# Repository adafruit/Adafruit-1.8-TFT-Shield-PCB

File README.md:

## Adafruit 1.8" 18-bit Color TFT Shield w/microSD and Joystick PCB

<a href="http://www.adafruit.com/products/802"><br/>
Click here to purchase one from the Adafruit shop</a>

PCB files for the Adafruit 1.8" 18-bit Color TFT Shield. Format is EagleCAD schematic and board layout
* https://www.adafruit.com/product/802

### Description

This lovely little shield is the best way to add a small, colorful and bright display to any project. We took our popular 1.8" TFT breakout board and remixed it into an Arduino shield complete with microSD card slot and a 5-way joystick navigation switch and three selection buttons! Since the display uses only 4 pins to communicate and has its own pixel-addressable frame buffer, it can be used easily to add a display & interface without exhausting the memory or pins.

New! We've updated this shield to be 'Arduino R3' format compatible so you can now use it with any and all Arduinos or Metros - including the Metro M0 or M4, Arduino Mega, Zero, etc. We also use Adafruit seesaw for the TFT backlight, TFT reset, and button inputs - you can query the buttons and joystick over I2C now, so only 2 pins are needed to communicate with all 8 switches.

The 1.8" display has 128x160 color pixels. Unlike the low cost "Nokia 6110" and similar LCD displays, which are CSTN type and thus have poor color and slow refresh, this display is a true TFT! The TFT driver (ST7735R) can display full 18-bit color (262,144 shades!).

The shield has the TFT display soldered on (it uses a delicate flex-circuit connector) as well as a ultra-low-dropout 3.3V regulator and a 3/5V level shifter so its safe to use with 3V or 5V Arduino compatibles. We also had some space left over so we placed a microSD card holder (so you can easily load full color bitmaps from a FAT16/FAT32 formatted microSD card), a 5-way navigation switch (left, right, up, down, select) and three tactile buttons marked A BC. The microSD card is not included, but you can pick one up here.

If you just want to display text, shapes, lines, pixels, etc the shield uses the SPI pins (SCK/MOSI/MISO), I2C pins (SDA & SCL) and digital #8. For the microSD card, you'll also give up Digital #4. This shield works with any Arduino UNO and compatibles, Mega, Zero, etc. If it's shield compatible, you're good to go.

### License

Adafruit invests time and resources providing this open source design, please support Adafruit and open-source hardware by purchasing products from [Adafruit](https://www.adafruit.com)!

Designed by Limor Fried/Ladyada for Adafruit Industries.

Creative Commons Attribution/Share-Alike, all text above must be included in any redistribution. See license.txt for additional details.

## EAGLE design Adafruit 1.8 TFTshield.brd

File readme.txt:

Adafruit 1.8" 18-bit Color TFT Shield w/microSD and Joystick 

These are the Eagle CAD files for the Adafruit 1.8" 18-bit Color TFT Shield w/microSD and Joystick - for Arduino:
  ----> http://www.adafruit.com/products/802

Adafruit invests time and resources providing this open source design, please support Adafruit and open-source hardware by purchasing products from Adafruit!

This lovely little shield is the best way to add a small, colorful and bright display to any project. We took our popular 1.8" TFT breakout board and remixed it into an Arduino shield complete with microSD card slot and a 5-way joystick navigation switch (with a nice plastic knob)! Since the display uses only 4 pins to communicate and has its own pixel-addressable frame buffer, it can be used easily to add a display & interface without exhausting the memory or pins. 

All text above must be included in any redistribution

Designed by Limor Fried/Ladyada for Adafruit Industries.
Creative Commons Attribution/Share-Alike, all text above must be included in any redistribution

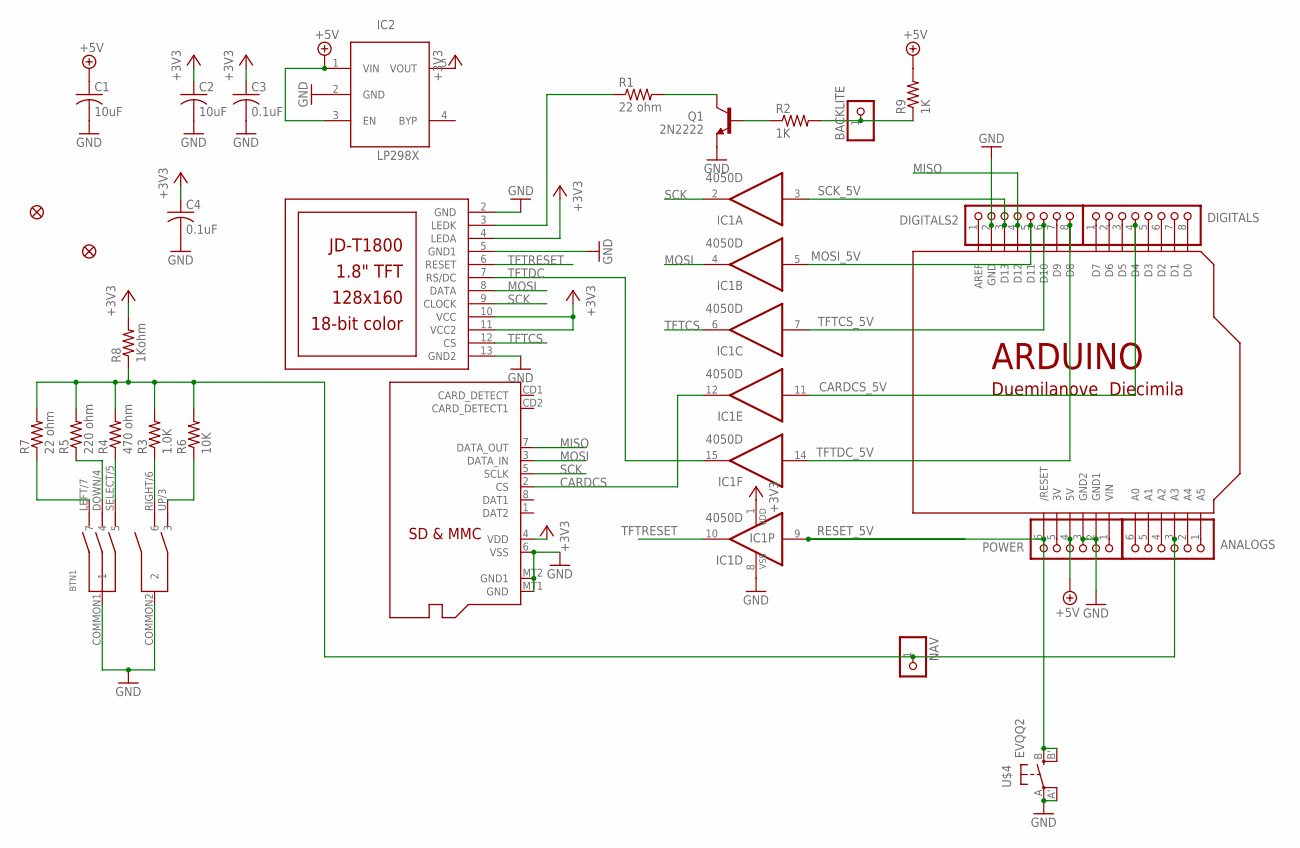
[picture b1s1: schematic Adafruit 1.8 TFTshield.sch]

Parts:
ANALOGS: PINHD-1X6CB; 1X06-CLEANBIG
BACKLITE: PINHD-1X1; 1X01
BTN1: SWITCH_4WAY_TPA511GLFS
C1, C2: 10uF; C0805K
C3, C4: 0.1uF; C0805K
DIGITALS, DIGITALS2: PINHD-1X8CLEANBIG; 1X08-CLEANBIG
FID1, FID3: FIDUCIAL1X2.5; FIDUCIAL-1X2.5
IC1: 4050D; SO16
IC2: RT9193-33GB; SOT23-5L
NAV: PINHD-1X1; 1X01
POWER: PINHD-1X6CB; 1X06-CLEANBIG
Q1: 2N2222; SOT23-BEC
R1, R7: 22 ohm; R0805
R2, R9: 1K; R0805
R3: 1.0K; R0805
R4: 470 ohm; R0805
R5: 220 ohm; R0805
R6: 10K; R0805
R8: 1Kohm; R0805
U$1: JD-T1800
U$2: ARDUINOUNO; ARDUINO
U$3: MICROSD
U$4: EVQQ2; EVQ-Q2

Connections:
+3V3: C2.1, C3.1, C4.1, IC1.1 (VDD), IC2.5 (VOUT), R8.2, U$1.4 (LEDA), U$1.10 (VCC), U$1.11 (VCC2), U$3.4 (VDD)
+5V: C1.1, IC2.1 (VIN), IC2.3 (EN), POWER.4, R9.2, U$2.5V
CARDCS: IC1.12 (O), U$3.2 (CS)
CARDCS_5V: DIGITALS.4, IC1.11 (I), U$2.D4
GND: BTN1.COMMON1 (1), BTN1.COMMON2 (2), C1.2, C2.2, C3.2, C4.2, DIGITALS2.2, IC1.8 (VSS), IC2.2 (GND), POWER.2, POWER.3, Q1.E, U$1.2 (GND), U$1.5 (GND1), U$1.13 (GND2), U$2.GND, U$2.GND1, U$2.GND2, U$3.6 (VSS), U$3.MT1 (GND), U$3.MT2 (GND1), U$4.A, U$4.A' (P1)
MISO: DIGITALS2.4, U$2.D12, U$3.7 (DATA_OUT)
MOSI: IC1.4 (O), U$1.8 (DATA), U$3.3 (DATA_IN)
MOSI_5V: DIGITALS2.5, IC1.5 (I), U$2.D11
unnamed: Q1.B, R2.1
unnamed: BTN1.LEFT/7 (7), R7.1
unnamed: BTN1.DOWN/4 (4), R5.1
unnamed: R1.1, U$1.3 (LEDK)
unnamed: Q1.C, R1.2
unnamed: DIGITALS2.7, U$2.D9
unnamed: BTN1.SELECT/5 (5), R4.1
unnamed: BTN1.RIGHT/6 (6), R3.1
unnamed: BTN1.UP/3 (3), R6.1
unnamed: ANALOGS.3, NAV.1, R3.2, R4.2, R5.2, R6.2, R7.2, R8.1, U$2.A3
unnamed: DIGITALS.1, U$2.D7
unnamed: DIGITALS.2, U$2.D6
unnamed: DIGITALS.3, U$2.D5
unnamed: DIGITALS.5, U$2.D3
unnamed: DIGITALS.6, U$2.D2
unnamed: DIGITALS.7, U$2.D1
unnamed: DIGITALS.8, U$2.D0
unnamed: DIGITALS2.1, U$2.AREF
unnamed: ANALOGS.1, U$2.A5
unnamed: ANALOGS.2, U$2.A4
unnamed: ANALOGS.4, U$2.A2
unnamed: ANALOGS.5, U$2.A1
unnamed: ANALOGS.6, U$2.A0
unnamed: POWER.1, U$2.VIN
unnamed: POWER.5, U$2.3V
unnamed: BACKLITE.1, R2.2, R9.1
RESET_5V: IC1.9 (I), POWER.6, U$2.RESET (/RESET), U$4.B (S), U$4.B' (S1)
SCK: IC1.2 (O), U$1.9 (CLOCK), U$3.5 (SCLK)
SCK_5V: DIGITALS2.3, IC1.3 (I), U$2.D13
TFTCS: IC1.6 (O), U$1.12 (CS)
TFTCS_5V: DIGITALS2.6, IC1.7 (I), U$2.D10
TFTDC: IC1.15 (O), U$1.7 (RS/DC)
TFTDC_5V: DIGITALS2.8, IC1.14 (I), U$2.D8
TFTRESET: IC1.10 (O), U$1.6 (RESET)

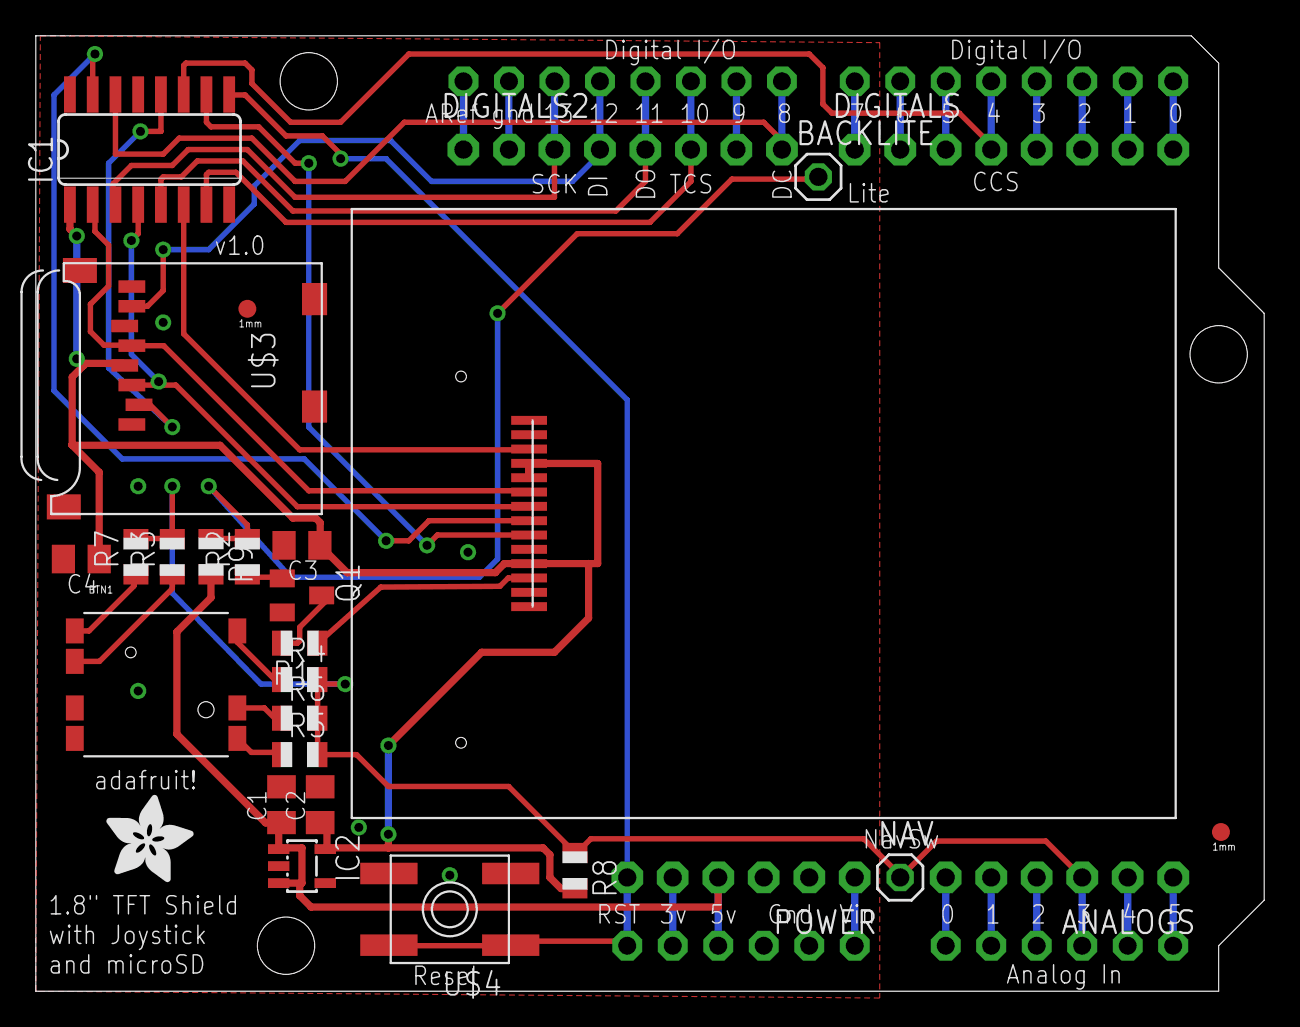
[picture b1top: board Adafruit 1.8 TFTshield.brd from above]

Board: 2 copper layers, 68.6 x 53.3 mm, 31 parts (1 on the bottom side), 42 nets.

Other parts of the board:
U$5: ADAFRUIT_TEXT_30MM
U$6: ADAFRUIT_5MM

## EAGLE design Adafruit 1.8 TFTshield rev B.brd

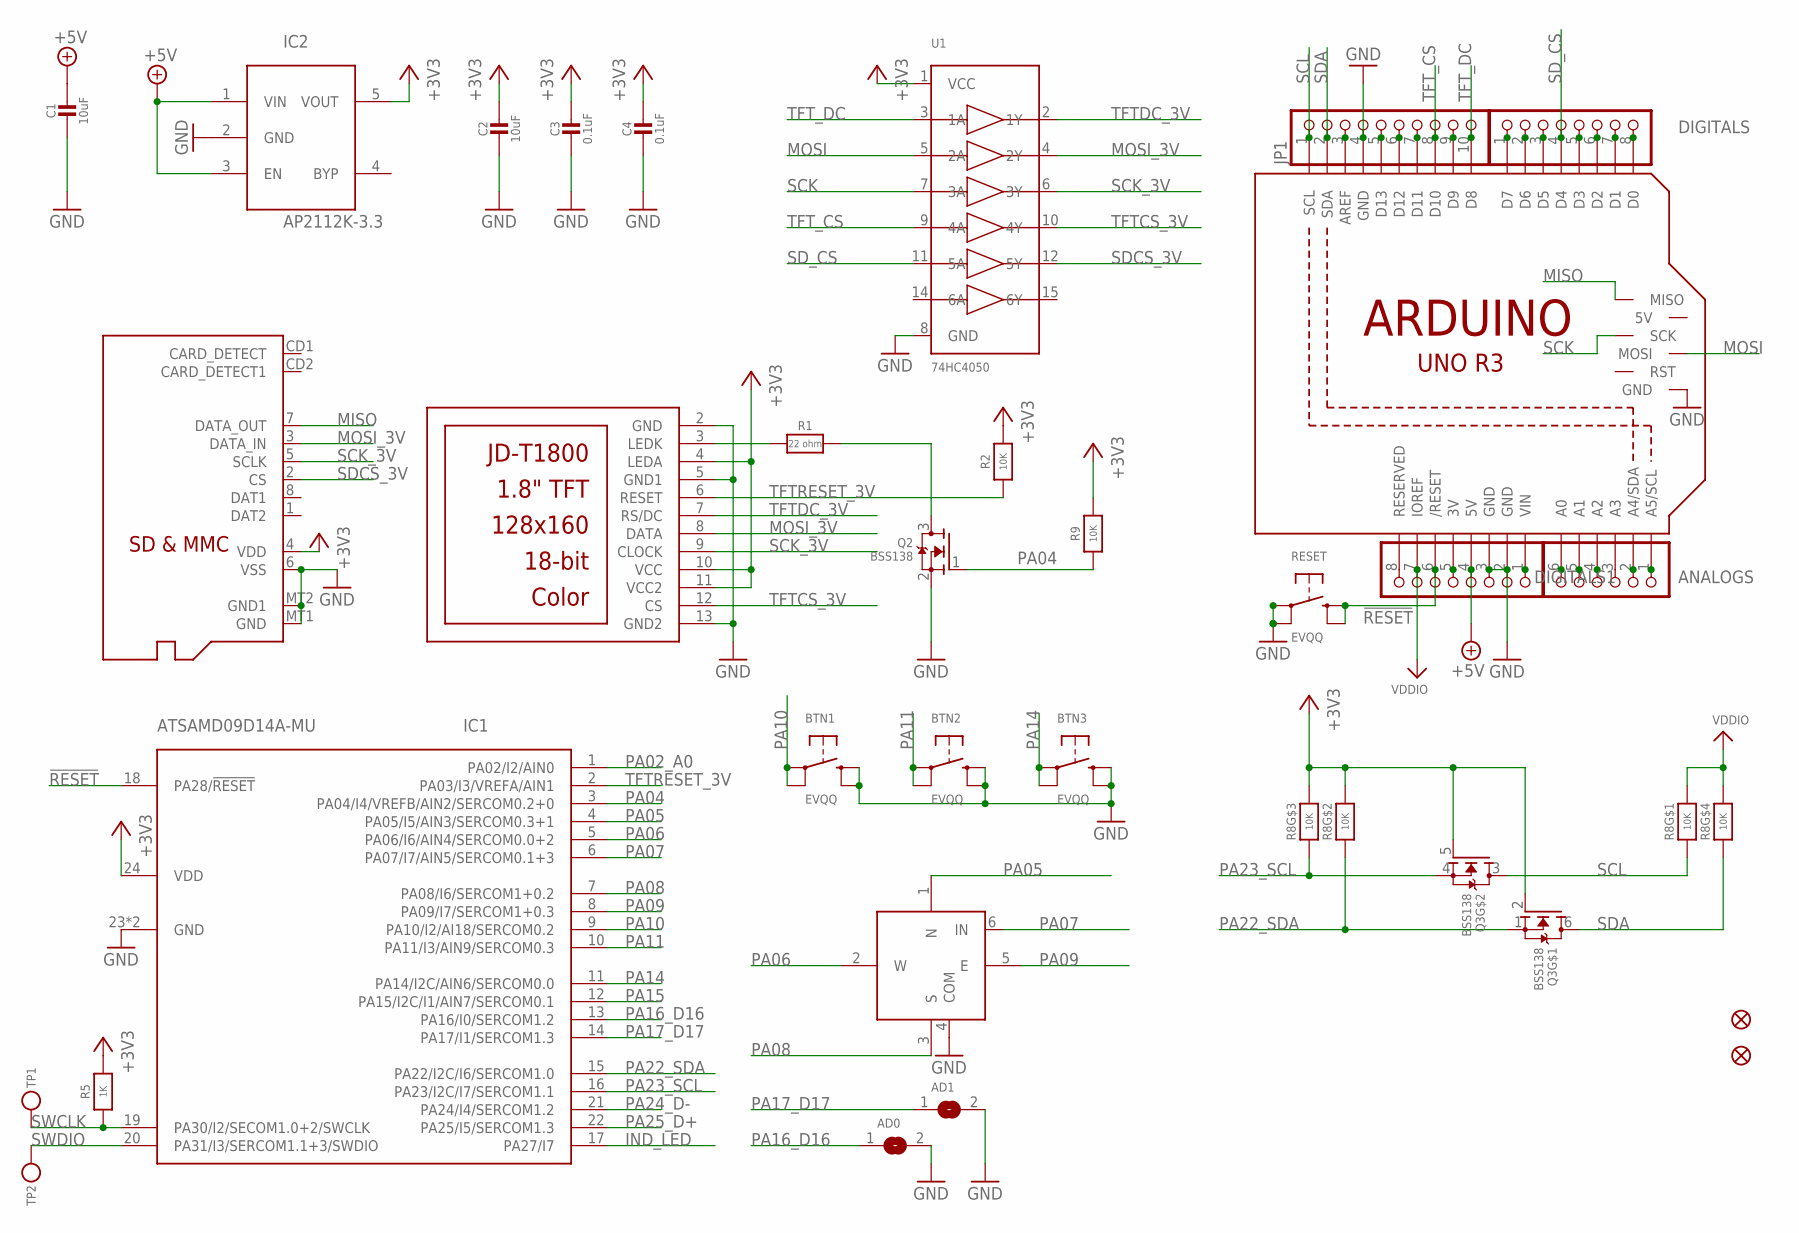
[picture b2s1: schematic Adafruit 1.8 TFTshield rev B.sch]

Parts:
AD0, AD1: SOLDERJUMPER; SOLDERJUMPER_ARROW_NOPASTE
ANALOGS: HEADER-1X6ROUND; 1X06_ROUND
BTN1, BTN2, BTN3: EVQQ; EVQ-Q2_SMALLER
C1, C2: 10uF; 0805-NO
C3, C4: 0.1uF; 0805-NO
DIGITALS, DIGITALS1: HEADER-1X8ROUND; 1X08_ROUND
FID1, FID3: FIDUCIAL_1MM
IC1: ATSAMD09D14A-MU; QFN24_4MM
IC2: AP2112K-3.3; SOT23-5L
JP1: HEADER-1X10ROUND; 1X10_ROUND
M1: ARDUINO_R3_ICSP; ARDUINOR3_ICSP
Q2: BSS138; SOT23-WIDE
Q3: BSS138; SOT363
R1: 22 ohm; 0805-NO
R2, R9: 10K; 0805-NO
R5: 1K; 0805-NO
R8: 10K; RESPACK_4X0603_NO
RESET: EVQQ; EVQ-Q2_SMALLER
SW1: NAVSWITCHSKQUABAUE010; SKQUBAE010
TP1, TP2: TESTPOINTROUND2MM; TESTPOINT_ROUND_2MM
U1: 74HC4050; TSSOP16
U$1: DISP_LCD_JDT1800; JD-T1800
U$3: MICROSD

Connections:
!RESET: DIGITALS1.6, IC1.18 (PA28/!RESET), M1.RESET (/RESET), RESET.B (S), RESET.B' (S1)
+3.3V: DIGITALS1.5, M1.3V
+3V3: C2.1, C3.1, C4.1, IC1.24 (VDD), IC2.5 (VOUT), Q3.2 (G), Q3.5 (G), R2.2, R5.2, R8.6 (2), R8.7 (2), R9.2, U1.1 (VCC), U$1.4 (LEDA), U$1.10 (VCC), U$1.11 (VCC2), U$3.4 (VDD)
+5V: C1.1, DIGITALS1.4, IC2.1 (VIN), IC2.3 (EN), M1.5V
A0: ANALOGS.6, M1.A0
A1: ANALOGS.5, M1.A1
A2: ANALOGS.4, M1.A2
A4: ANALOGS.2, M1.A4 (A4/SDA)
A5: ANALOGS.1, M1.A5 (A5/SCL)
AREF: JP1.3, M1.AREF
D0: DIGITALS.8, M1.D0
D1: DIGITALS.7, M1.D1
D2: DIGITALS.6, M1.D2
D3: DIGITALS.5, M1.D3
D5: DIGITALS.3, M1.D5
D6: DIGITALS.2, M1.D6
D7: DIGITALS.1, M1.D7
D9: JP1.9, M1.D9
GND: AD0.2, AD1.2, BTN1.B (S), BTN1.B' (S1), BTN2.B (S), BTN2.B' (S1), BTN3.B (S), BTN3.B' (S1), C1.2, C2.2, C3.2, C4.2, DIGITALS1.2, DIGITALS1.3, IC1.23 (GND), IC1.THERM (GND), IC2.2 (GND), JP1.4, M1.GND, M1.GND@1 (GND), M1.GND@2 (GND), M1.GND@3 (GND), Q2.2 (S), RESET.A, RESET.A' (P1), SW1.4 (COM), U1.8 (GND), U$1.2 (GND), U$1.5 (GND1), U$1.13 (GND2), U$3.6 (VSS), U$3.MT1 (GND), U$3.MT2 (GND1)
IND_LED: IC1.17 (PA27/I7)
MISO: M1.MISO, U$3.7 (DATA_OUT)
MOSI: M1.MOSI, U1.5 (2A)
MOSI_3V: U1.4 (2Y), U$1.8 (DATA), U$3.3 (DATA_IN)
unnamed: R1.1, U$1.3 (LEDK)
unnamed: Q2.3 (D), R1.2
unnamed: JP1.5, M1.D13
unnamed: JP1.6, M1.D12
unnamed: JP1.7, M1.D11
unnamed: ANALOGS.3, M1.A3
unnamed: DIGITALS1.8, M1.RESERVED
PA02_A0: IC1.1 (PA02/I2/AIN0)
PA04: IC1.3 (PA04/I4/VREFB/AIN2/SERCOM0.2+0), Q2.1 (G), R9.1
PA05: IC1.4 (PA05/I5/AIN3/SERCOM0.3+1), SW1.1 (N)
PA06: IC1.5 (PA06/I6/AIN4/SERCOM0.0+2), SW1.2 (W)
PA07: IC1.6 (PA07/I7/AIN5/SERCOM0.1+3), SW1.6 (IN)
PA08: IC1.7 (PA08/I6/SERCOM1+0.2), SW1.3 (S)
PA09: IC1.8 (PA09/I7/SERCOM1+0.3), SW1.5 (E)
PA10: BTN1.A, BTN1.A' (P1), IC1.9 (PA10/I2/AI18/SERCOM0.2)
PA11: BTN2.A, BTN2.A' (P1), IC1.10 (PA11/I3/AIN9/SERCOM0.3)
PA14: BTN3.A, BTN3.A' (P1), IC1.11 (PA14/I2C/AIN6/SERCOM0.0)
PA15: IC1.12 (PA15/I2C/I1/AIN7/SERCOM0.1)
PA16_D16: AD0.1, IC1.13 (PA16/I0/SERCOM1.2)
PA17_D17: AD1.1, IC1.14 (PA17/I1/SERCOM1.3)
PA22_SDA: IC1.15 (PA22/I2C/I6/SERCOM1.0), Q3.1 (S), R8.2 (1)
PA23_SCL: IC1.16 (PA23/I2C/I7/SERCOM1.1), Q3.4 (S), R8.3 (1)
PA24_D-: IC1.21 (PA24/I4/SERCOM1.2)
PA25_D+: IC1.22 (PA25/I5/SERCOM1.3)
SCK: M1.SCK, U1.7 (3A)
SCK_3V: U1.6 (3Y), U$1.9 (CLOCK), U$3.5 (SCLK)
SCL: JP1.1, M1.SCL, Q3.3 (D), R8.1
SDA: JP1.2, M1.SDA, Q3.6 (D), R8.4 (1)
SDCS_3V: U1.12 (5Y), U$3.2 (CS)
SD_CS: DIGITALS.4, M1.D4, U1.11 (5A)
SWCLK: IC1.19 (PA30/I2/SECOM1.0+2/SWCLK), R5.1, TP1.P$1
SWDIO: IC1.20 (PA31/I3/SERCOM1.1+3/SWDIO), TP2.P$1
TFTCS_3V: U1.10 (4Y), U$1.12 (CS)
TFTDC_3V: U1.2 (1Y), U$1.7 (RS/DC)
TFTRESET_3V: IC1.2 (PA03/I3/VREFA/AIN1), R2.1, U$1.6 (RESET)
TFT_CS: JP1.8, M1.D10, U1.9 (4A)
TFT_DC: JP1.10, M1.D8, U1.3 (1A)
VDDIO: DIGITALS1.7, M1.IOREF, R8.5 (2), R8.8 (2)
VIN: DIGITALS1.1, M1.VIN

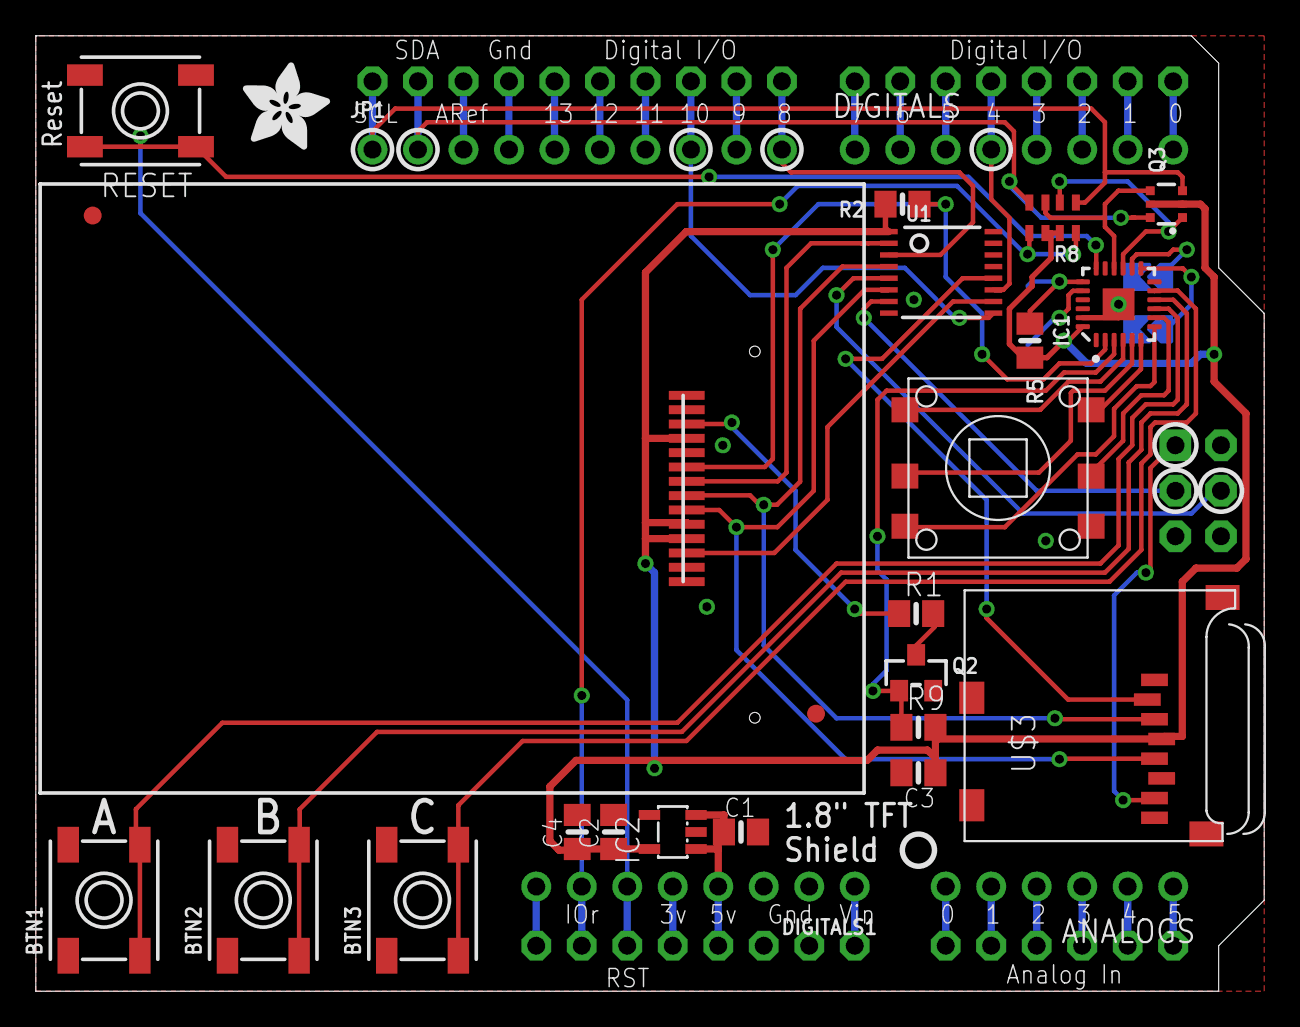
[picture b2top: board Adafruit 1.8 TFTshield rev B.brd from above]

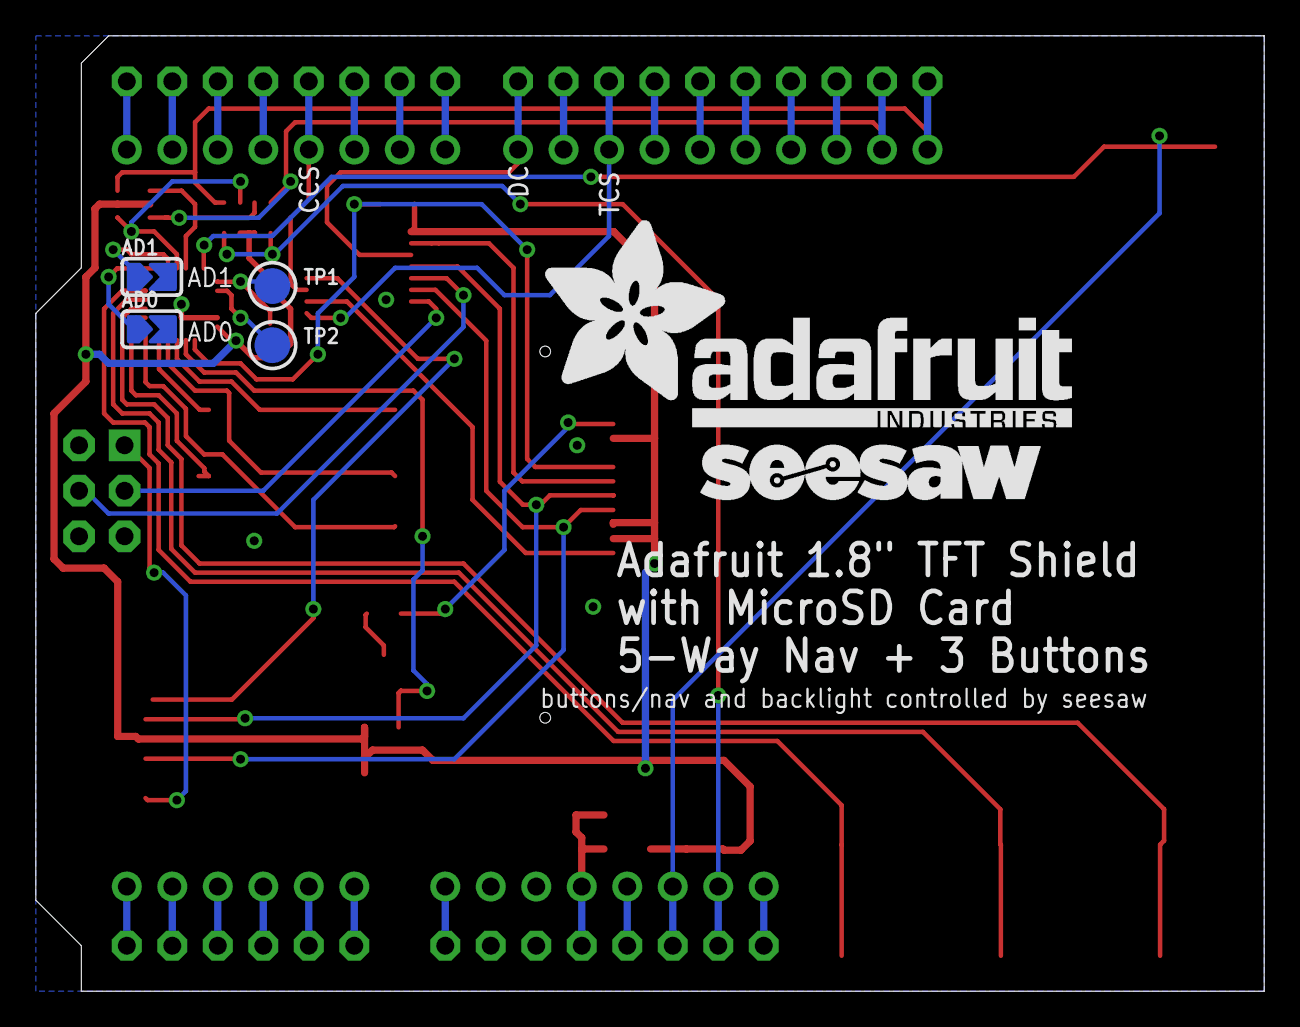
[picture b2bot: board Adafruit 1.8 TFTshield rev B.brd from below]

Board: 2 copper layers, 68.6 x 53.3 mm, 36 parts (6 on the bottom side), 57 nets.

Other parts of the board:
U$5: ADAFRUIT_TEXT_30MM
U$7: ADAFRUIT_5MM
U$8: SEESAW_LOGO
U$9: PCBFEAT-REV-040

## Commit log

2012-07-24 init
2018-08-26 https://github.com/adafruit/Adafruit-1.8-TFT-Shield-PCB/issues/1
2019-07-15 updating repo to new template
2026-06-03 update file format to XML
